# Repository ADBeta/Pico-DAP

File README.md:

# Pico-DAP
Pico-DAP is a CMSIS-DAP and Virtual COM Port (VCP) Device for programming
ARM based Microcontrollers, based on the `RP2040` Raspberry Pi Pico 
architecture, using the Pico-SDK toolchain.  

This reason for this project is to perfect the CMSIS-DAP device handling for
one specific device, without the worry of porting in the future.  
The project is open to the community and any ideas you have.  

## Flashing
`pico-dap.bin` and `pico-dap.uf2` files are available in the 
[Binaries](/Firmware/bins) directory.  
Use the `.uf2` if you are flashing via USB bootloader, or `.bin` if you are 
flashing via SWD.

## PCBs
### Pico-DAP-Zero
The original PCB for this project, using an aftermarket Pico Zero Development
board  
<div style="display: flex; align-items: center; gap: 10px;">

</div>

## TODO
* Move free-dap to a Pico-SDK Project
* Make a PCB for the regular Pico
* Make a PCB for a bare RP2040
* Change USB VID and PID

## Possible Changes
* Add CH32V SWIO Support
* Make specific JTAG USB Adatper

----
ADBeta (c) 2024

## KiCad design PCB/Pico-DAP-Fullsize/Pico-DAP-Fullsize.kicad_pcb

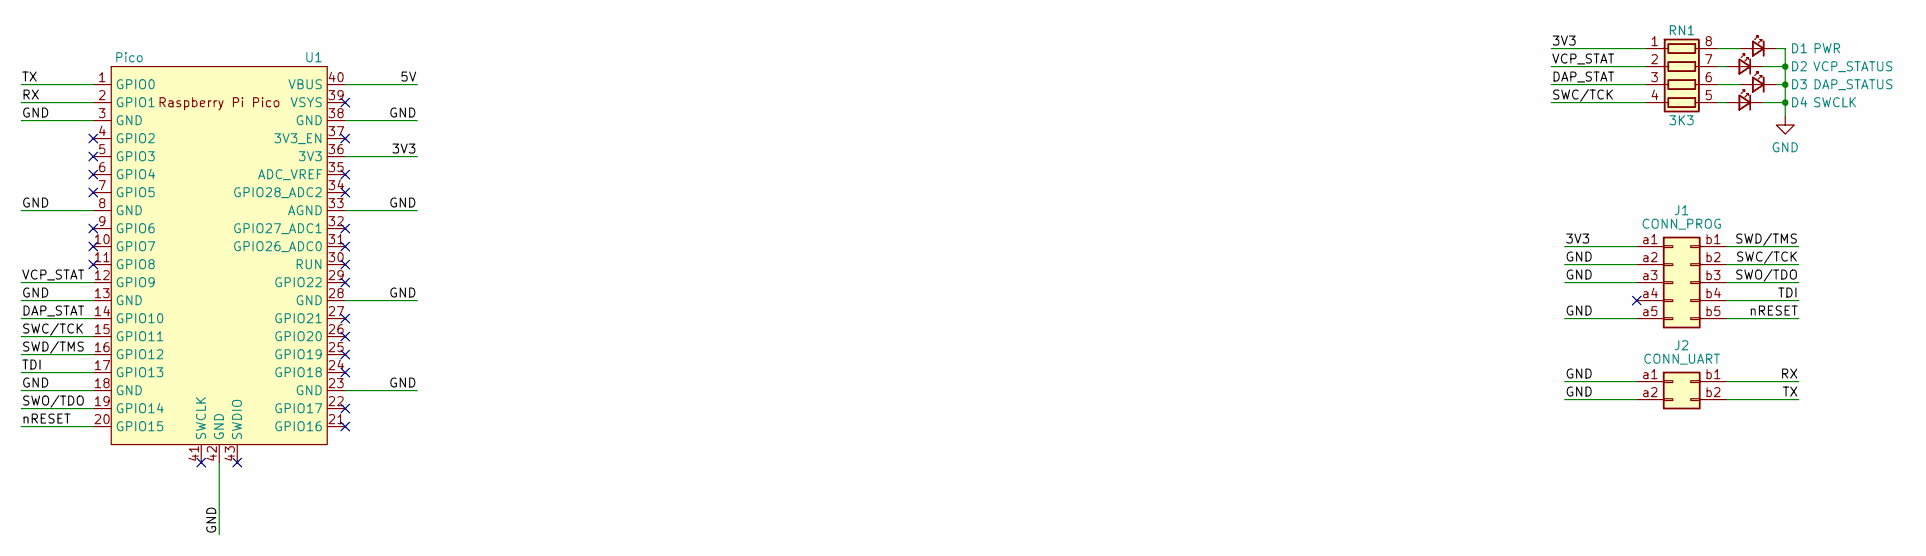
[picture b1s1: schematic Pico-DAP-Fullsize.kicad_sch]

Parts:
D1: PWR; LED_0402_1005Metric_Pad0.77x0.64mm_HandSolder
D2: VCP_STATUS; LED_0402_1005Metric_Pad0.77x0.64mm_HandSolder
D3: DAP_STATUS; LED_0402_1005Metric_Pad0.77x0.64mm_HandSolder
D4: SWCLK; LED_0402_1005Metric_Pad0.77x0.64mm_HandSolder
J1: CONN_PROG; Conn_2x5_Dual_Side
J2: CONN_UART; Conn_2x2_Dual_Side
RN1: 3K3; R_Array_Convex_4x0603
U1: Pico; RPi_Pico_SMD_TH

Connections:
/3V3: J1.a1, RN1.1 (R1.1), U1.36 (3V3)
/5V: U1.40 (VBUS)
/DAP_STAT: RN1.3 (R3.1), U1.14 (GPIO10)
/RX: J2.b1, U1.2 (GPIO1)
/SWC/TCK: J1.b2, RN1.4 (R4.1), U1.15 (GPIO11)
/SWD/TMS: J1.b1, U1.16 (GPIO12)
/SWO/TDO: J1.b3, U1.19 (GPIO14)
/TDI: J1.b4, U1.17 (GPIO13)
/TX: J2.b2, U1.1 (GPIO0)
/VCP_STAT: RN1.2 (R2.1), U1.12 (GPIO9)
/nRESET: J1.b5, U1.20 (GPIO15)
GND: D1.1 (K), D2.1 (K), D3.1 (K), D4.1 (K), J1.a2, J1.a3, J1.a5, J2.a1, J2.a2, U1.3 (GND), U1.8 (GND), U1.13 (GND), U1.18 (GND), U1.23 (GND), U1.28 (GND), U1.33 (AGND), U1.38 (GND), U1.42 (GND)
unnamed: D1.2 (A), RN1.8 (R1.2)
unnamed: D2.2 (A), RN1.7 (R2.2)
unnamed: D3.2 (A), RN1.6 (R3.2)
unnamed: D4.2 (A), RN1.5 (R4.2)

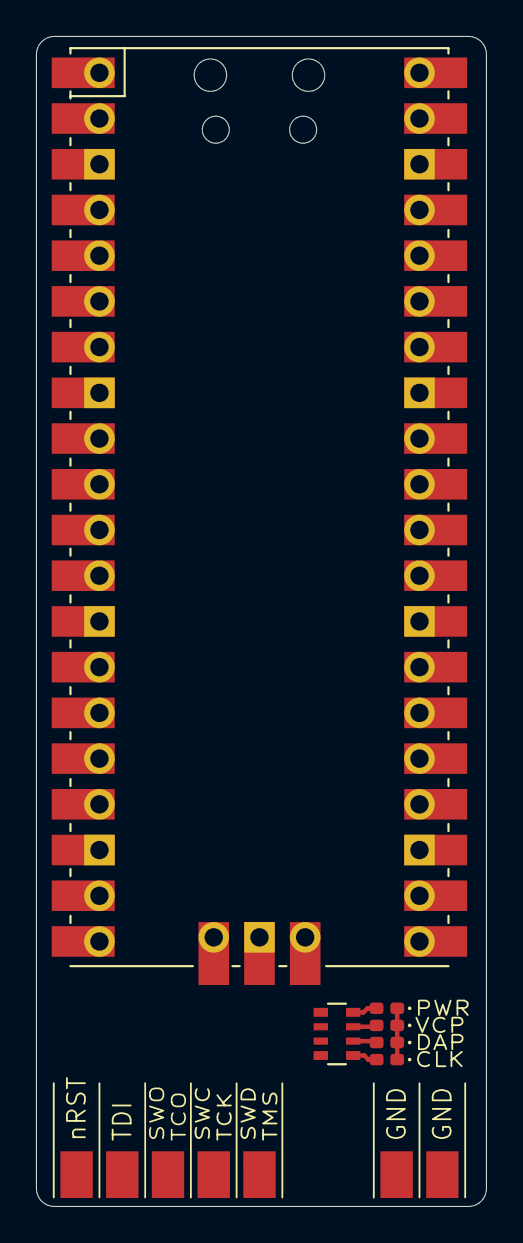
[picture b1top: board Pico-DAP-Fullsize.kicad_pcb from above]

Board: 2 copper layers, 25.0 x 65.0 mm, 8 parts (1 on the bottom side), 15 nets.

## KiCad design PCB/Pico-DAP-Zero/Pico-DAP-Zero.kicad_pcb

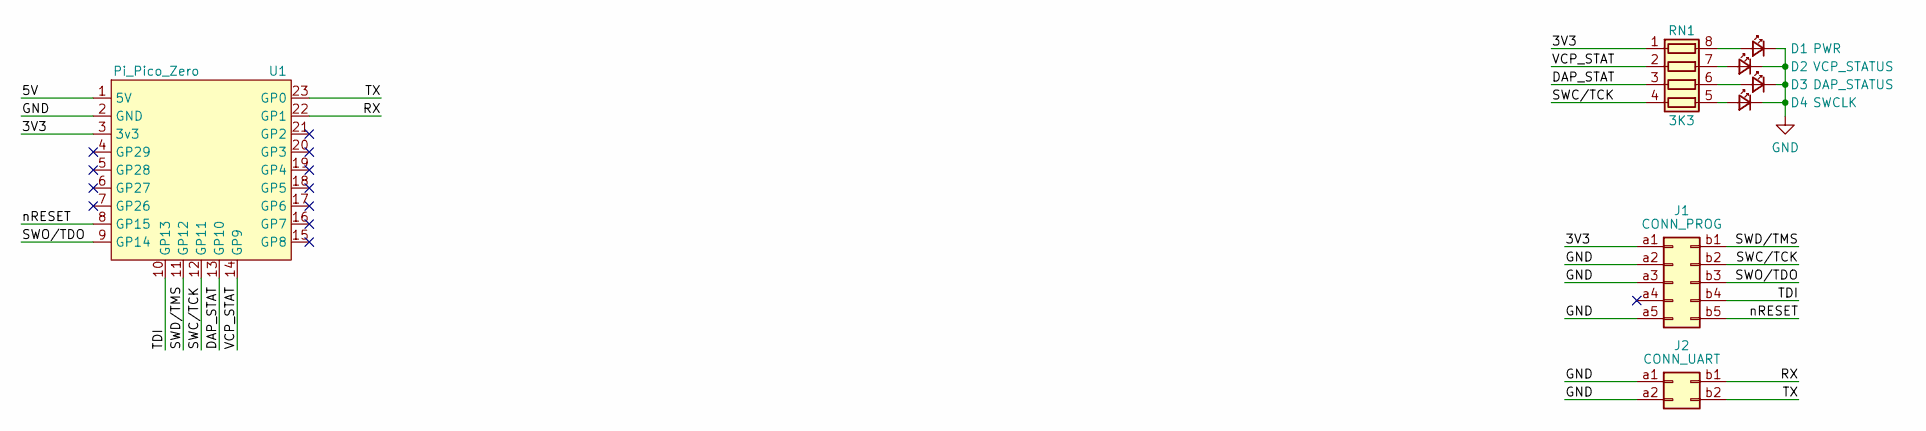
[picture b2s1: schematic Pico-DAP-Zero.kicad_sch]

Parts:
D1: PWR; LED_0402_1005Metric_Pad0.77x0.64mm_HandSolder
D2: VCP_STATUS; LED_0402_1005Metric_Pad0.77x0.64mm_HandSolder
D3: DAP_STATUS; LED_0402_1005Metric_Pad0.77x0.64mm_HandSolder
D4: SWCLK; LED_0402_1005Metric_Pad0.77x0.64mm_HandSolder
J1: CONN_PROG; Conn_2x5_Dual_Side
J2: CONN_UART; Conn_2x2_Dual_Side
RN1: 3K3; R_Array_Convex_4x0603
U1: Pi_Pico_Zero; Pi_Pico_Zero_Center_Hole

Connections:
/3V3: J1.a1, RN1.1 (R1.1), U1.3 (3v3)
/5V: U1.1 (5V)
/DAP_STAT: RN1.3 (R3.1), U1.13 (GP10)
/RX: J2.b1, U1.22 (GP1)
/SWC/TCK: J1.b2, RN1.4 (R4.1), U1.12 (GP11)
/SWD/TMS: J1.b1, U1.11 (GP12)
/SWO/TDO: J1.b3, U1.9 (GP14)
/TDI: J1.b4, U1.10 (GP13)
/TX: J2.b2, U1.23 (GP0)
/VCP_STAT: RN1.2 (R2.1), U1.14 (GP9)
/nRESET: J1.b5, U1.8 (GP15)
GND: D1.1 (K), D2.1 (K), D3.1 (K), D4.1 (K), J1.a2, J1.a3, J1.a5, J2.a1, J2.a2, U1.2 (GND)
unnamed: D1.2 (A), RN1.8 (R1.2)
unnamed: D2.2 (A), RN1.7 (R2.2)
unnamed: D3.2 (A), RN1.6 (R3.2)
unnamed: D4.2 (A), RN1.5 (R4.2)

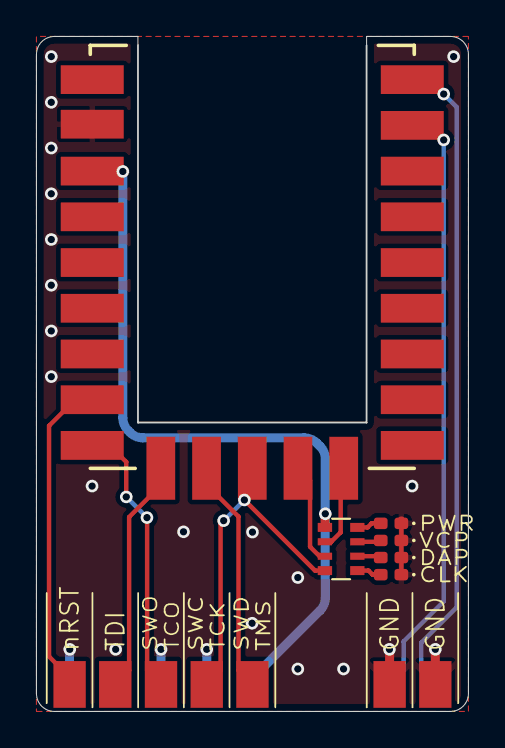
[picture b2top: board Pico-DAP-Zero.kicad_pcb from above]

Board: 2 copper layers, 23.9 x 37.5 mm, 8 parts (1 on the bottom side), 15 nets.

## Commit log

2024-11-20 Restructured file tree
2024-11-21 MkI PCB Final
2024-11-22 Added Firmware Original
2024-11-22 Fixed makefile, added dap.c/.h
2024-11-22 Changed LED Pinout
2024-11-23 Renamed PCB
2024-11-23 Changed License to BSD-3
2024-11-23 Changed USB Descriptors
2024-11-23 Renamed project
2024-11-23 Changed PCB Silkscreen
2024-11-23 Added README
2024-11-23 Scaled up README Images
2024-11-26 Added fullsize PCB
2024-11-26 Started to remove rp2040.h and uart.h
2024-11-26 cleanup
2024-11-29 Starting UART changeover
2024-12-01 Updated Mk0 Binaries
2024-12-08 Rolled back Mk0 Files, built functional custom .uf2
2025-01-24 Started reverse engineering
2025-01-25 Changed copyright, making notes
2025-01-29 Added Pin Configuration and basic UART Setup
2025-01-31 UART Testing
2025-02-02 USB CDC Testing
2025-02-02 Added Descriptors
2025-02-02 Debugging USB
2025-02-03 Bugfixing USB
2025-02-07 Continued USB debugging
2025-02-08 Functional Test LED and Baudrate
2025-02-08 Updated version
2025-02-08 Begin ms without delay
2025-02-08 Migrated from sleep_ms
2025-02-10 Changed UART LED, and set all LED GPIO Pins
2025-02-12 SWD Protocol Research
2025-02-13 Started research
2025-02-15 DAP Notes
2025-02-22 Added DAP HID Commands
